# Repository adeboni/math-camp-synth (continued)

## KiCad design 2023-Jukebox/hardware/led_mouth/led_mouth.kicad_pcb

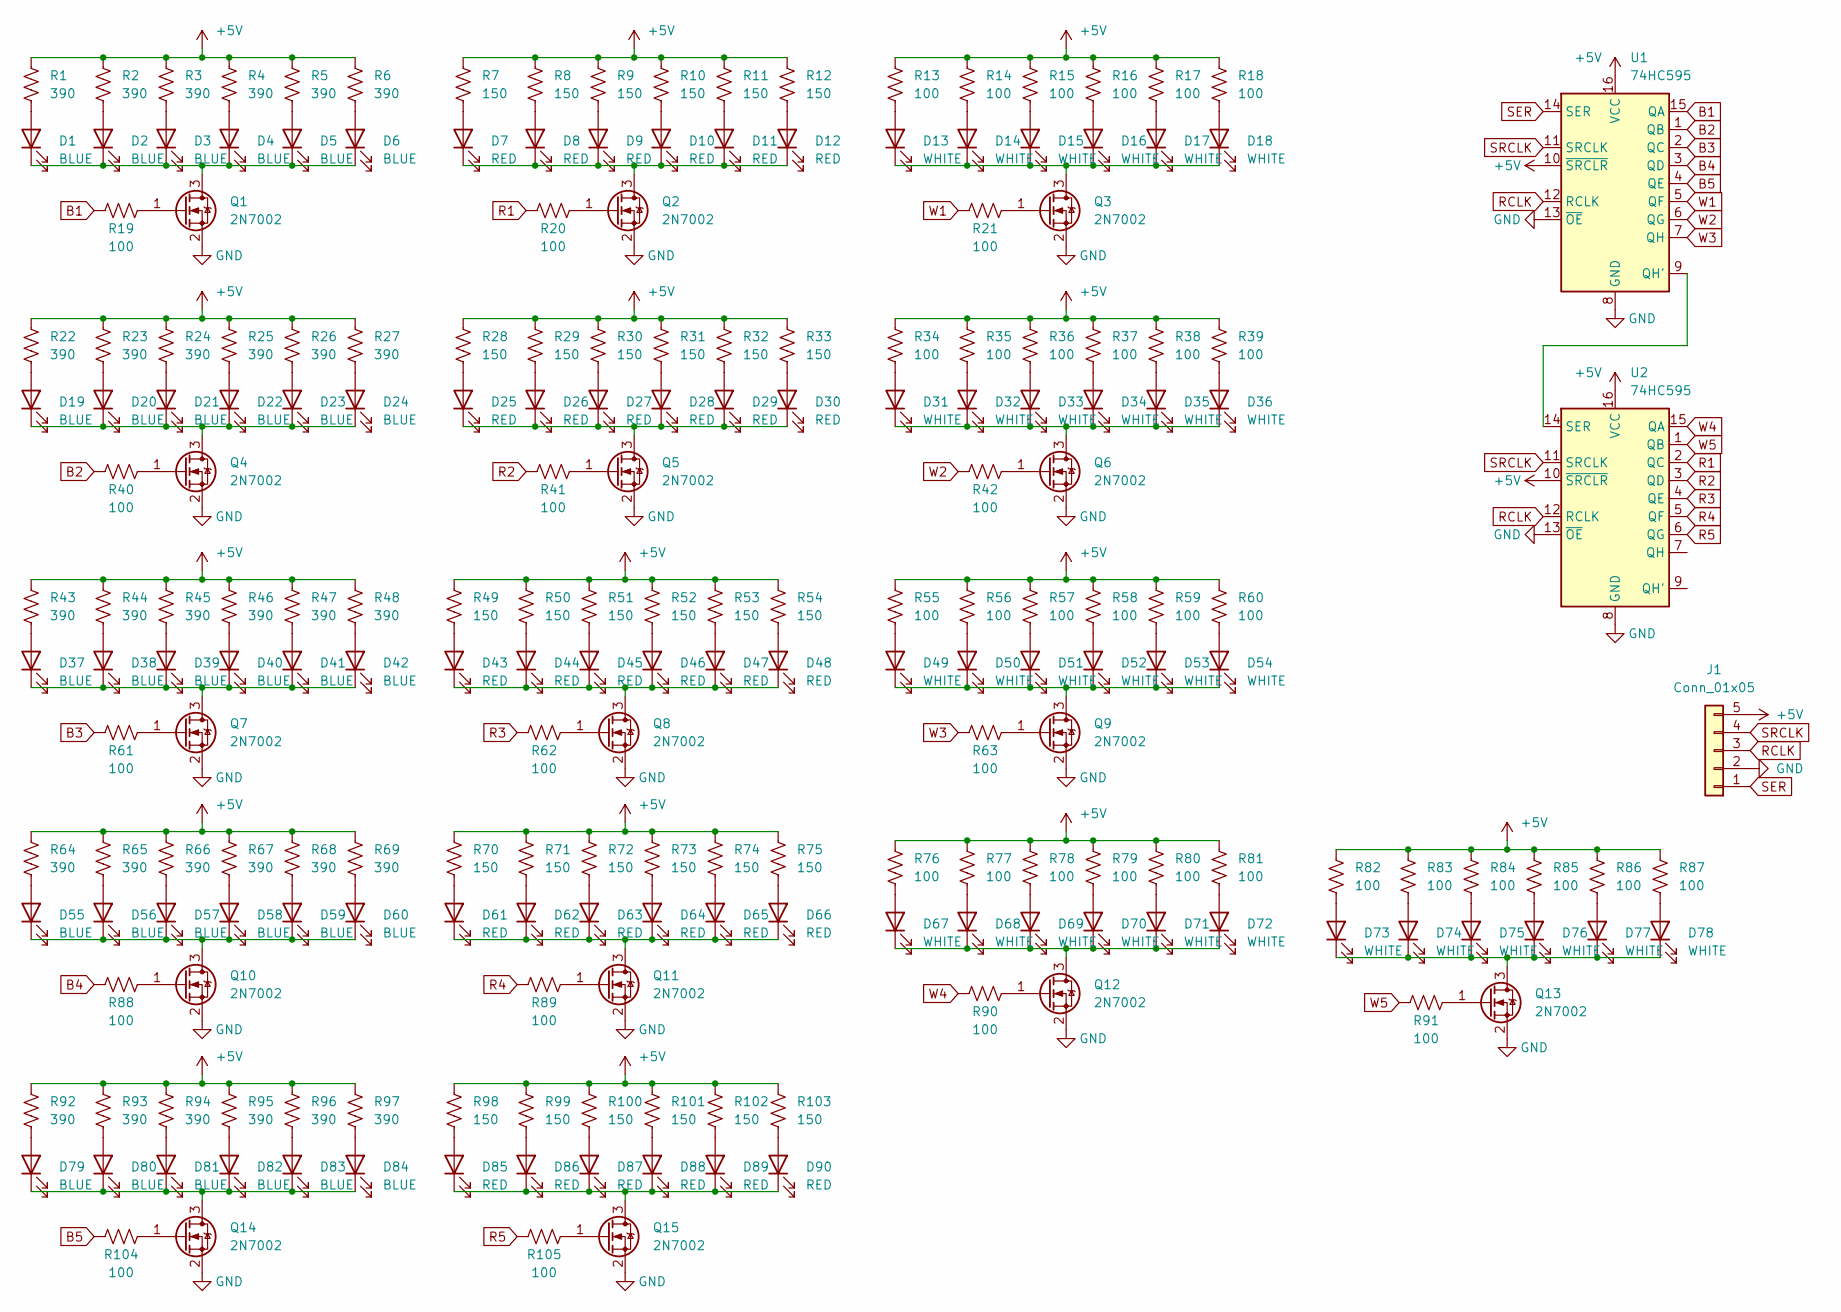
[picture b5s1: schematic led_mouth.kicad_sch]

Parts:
D1, D2, D3, D4, D5, D6, D19, D20, D21, D22, D23, D24, D37, D38, D39, D40, D41, D42, D55, D56, D57, D58, D59, D60, D79, D80, D81, D82, D83, D84: BLUE; LED_0603_1608Metric
D7, D8, D9, D10, D11, D12, D25, D26, D27, D28, D29, D30, D43, D44, D45, D46, D47, D48, D61, D62, D63, D64, D65, D66, D85, D86, D87, D88, D89, D90: RED; LED_0603_1608Metric
D13, D14, D15, D16, D17, D18, D31, D32, D33, D34, D35, D36, D49, D50, D51, D52, D53, D54, D67, D68, D69, D70, D71, D72, D73, D74, D75, D76, D77, D78: WHITE; LED_0603_1608Metric
J1: Conn_01x05
Q1, Q2, Q3, Q4, Q5, Q6, Q7, Q8, Q9, Q10, Q11, Q12, Q13, Q14, Q15: 2N7002; SOT-23
R1, R2, R3, R4, R5, R6, R22, R23, R24, R25, R26, R27, R43, R44, R45, R46, R47, R48, R64, R65, R66, R67, R68, R69, R92, R93, R94, R95, R96, R97: 390; R_0603_1608Metric
R7, R8, R9, R10, R11, R12, R28, R29, R30, R31, R32, R33, R49, R50, R51, R52, R53, R54, R70, R71, R72, R73, R74, R75, R98, R99, R100, R101, R102, R103: 150; R_0603_1608Metric
R13, R14, R15, R16, R17, R18, R20, R21, R34, R35, R36, R37, R38, R39, R40, R41, R42, R55, R56, R57, R58, R59, R60, R61, R62, R63, R76, R77, R78, R79, R80, R81, R82, R83, R84, R85, R86, R87, R88, R89, R90, R91, R104, R105: 100; R_0603_1608Metric
R19: 100
U1: 74HC595
U2: 74HC595; SOIC-16_3.9x9.9mm_P1.27mm

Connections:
+5V: J1.5, R1.2, R2.2, R3.2, R4.2, R5.2, R6.2, R7.2, R8.2, R9.2, R10.2, R11.2, R12.2, R13.2, R14.2, R15.2, R16.2, R17.2, R18.2, R22.2, R23.2, R24.2, R25.2, R26.2, R27.2, R28.2, R29.2, R30.2, R31.2, R32.2, R33.2, R34.2, R35.2, R36.2, R37.2, R38.2, R39.2, R43.2, R44.2, R45.2, R46.2, R47.2, R48.2, R49.2, R50.2, R51.2, R52.2, R53.2, R54.2, R55.2, R56.2, R57.2, R58.2, R59.2, R60.2, R64.2, R65.2, R66.2, R67.2, R68.2, R69.2, R70.2, R71.2, R72.2, R73.2, R74.2, R75.2, R76.2, R77.2, R78.2, R79.2, R80.2, R81.2, R82.2, R83.2, R84.2, R85.2, R86.2, R87.2, R92.2, R93.2, R94.2, R95.2, R96.2, R97.2, R98.2, R99.2, R100.2, R101.2, R102.2, R103.2, U1.10 (~SRCLR), U1.16 (VCC), U2.10 (~SRCLR), U2.16 (VCC)
B1: R19.1, U1.15 (QA)
B2: R40.1, U1.1 (QB)
B3: R61.1, U1.2 (QC)
B4: R88.1, U1.3 (QD)
B5: R104.1, U1.4 (QE)
GND: J1.2, Q1.2 (S), Q2.2 (S), Q3.2 (S), Q4.2 (S), Q5.2 (S), Q6.2 (S), Q7.2 (S), Q8.2 (S), Q9.2 (S), Q10.2 (S), Q11.2 (S), Q12.2 (S), Q13.2 (S), Q14.2 (S), Q15.2 (S), U1.8 (GND), U1.13 (~OE), U2.8 (GND), U2.13 (~OE)
unnamed: D1.1 (K), D2.1 (K), D3.1 (K), D4.1 (K), D5.1 (K), D6.1 (K), Q1.3 (D)
unnamed: D1.2 (A), R1.1
unnamed: D2.2 (A), R2.1
unnamed: D3.2 (A), R3.1
unnamed: D4.2 (A), R4.1
unnamed: D5.2 (A), R5.1
unnamed: D6.2 (A), R6.1
unnamed: D7.2 (A), R7.1
unnamed: D8.2 (A), R8.1
unnamed: D9.2 (A), R9.1
unnamed: D7.1 (K), D8.1 (K), D9.1 (K), D10.1 (K), D11.1 (K), D12.1 (K), Q2.3 (D)
unnamed: D10.2 (A), R10.1
unnamed: D11.2 (A), R11.1
unnamed: D12.2 (A), R12.1
unnamed: D13.1 (K), D14.1 (K), D15.1 (K), D16.1 (K), D17.1 (K), D18.1 (K), Q3.3 (D)
unnamed: D13.2 (A), R13.1
unnamed: D14.2 (A), R14.1
unnamed: D15.2 (A), R15.1
unnamed: D16.2 (A), R16.1
unnamed: D17.2 (A), R17.1
unnamed: D18.2 (A), R18.1
unnamed: D19.1 (K), D20.1 (K), D21.1 (K), D22.1 (K), D23.1 (K), D24.1 (K), Q4.3 (D)
unnamed: D19.2 (A), R22.1
unnamed: D20.2 (A), R23.1
unnamed: D21.2 (A), R24.1
unnamed: D22.2 (A), R25.1
unnamed: D23.2 (A), R26.1
unnamed: D24.2 (A), R27.1
unnamed: D25.1 (K), D26.1 (K), D27.1 (K), D28.1 (K), D29.1 (K), D30.1 (K), Q5.3 (D)
unnamed: D25.2 (A), R28.1
unnamed: D26.2 (A), R29.1
unnamed: D27.2 (A), R30.1
unnamed: D28.2 (A), R31.1
unnamed: D29.2 (A), R32.1
unnamed: D30.2 (A), R33.1
unnamed: D31.1 (K), D32.1 (K), D33.1 (K), D34.1 (K), D35.1 (K), D36.1 (K), Q6.3 (D)
unnamed: D31.2 (A), R34.1
unnamed: D32.2 (A), R35.1
unnamed: D33.2 (A), R36.1
unnamed: D34.2 (A), R37.1
unnamed: D35.2 (A), R38.1
unnamed: D36.2 (A), R39.1
unnamed: D37.1 (K), D38.1 (K), D39.1 (K), D40.1 (K), D41.1 (K), D42.1 (K), Q7.3 (D)
unnamed: D37.2 (A), R43.1
unnamed: D38.2 (A), R44.1
unnamed: D39.2 (A), R45.1
unnamed: D40.2 (A), R46.1
unnamed: D41.2 (A), R47.1
unnamed: D42.2 (A), R48.1
unnamed: D43.1 (K), D44.1 (K), D45.1 (K), D46.1 (K), D47.1 (K), D48.1 (K), Q8.3 (D)
unnamed: D43.2 (A), R49.1
unnamed: D44.2 (A), R50.1
unnamed: D45.2 (A), R51.1
unnamed: D46.2 (A), R52.1
unnamed: D47.2 (A), R53.1
unnamed: D48.2 (A), R54.1
unnamed: D49.1 (K), D50.1 (K), D51.1 (K), D52.1 (K), D53.1 (K), D54.1 (K), Q9.3 (D)
unnamed: D49.2 (A), R55.1
unnamed: D50.2 (A), R56.1
unnamed: D51.2 (A), R57.1
unnamed: D52.2 (A), R58.1
unnamed: D53.2 (A), R59.1
unnamed: D54.2 (A), R60.1
unnamed: D55.1 (K), D56.1 (K), D57.1 (K), D58.1 (K), D59.1 (K), D60.1 (K), Q10.3 (D)
unnamed: D55.2 (A), R64.1
unnamed: D56.2 (A), R65.1
unnamed: D57.2 (A), R66.1
unnamed: D58.2 (A), R67.1
unnamed: D59.2 (A), R68.1
unnamed: D60.2 (A), R69.1
unnamed: D61.1 (K), D62.1 (K), D63.1 (K), D64.1 (K), D65.1 (K), D66.1 (K), Q11.3 (D)
unnamed: D61.2 (A), R70.1
unnamed: D62.2 (A), R71.1
unnamed: D63.2 (A), R72.1
unnamed: D64.2 (A), R73.1
unnamed: D65.2 (A), R74.1
unnamed: D66.2 (A), R75.1
unnamed: D67.1 (K), D68.1 (K), D69.1 (K), D70.1 (K), D71.1 (K), D72.1 (K), Q12.3 (D)
unnamed: D67.2 (A), R76.1
unnamed: D68.2 (A), R77.1
unnamed: D69.2 (A), R78.1
unnamed: D70.2 (A), R79.1
unnamed: D71.2 (A), R80.1
unnamed: D72.2 (A), R81.1
unnamed: D73.1 (K), D74.1 (K), D75.1 (K), D76.1 (K), D77.1 (K), D78.1 (K), Q13.3 (D)
unnamed: D73.2 (A), R82.1
unnamed: D74.2 (A), R83.1
unnamed: D75.2 (A), R84.1
unnamed: D76.2 (A), R85.1
unnamed: D77.2 (A), R86.1
unnamed: D78.2 (A), R87.1
unnamed: D79.1 (K), D80.1 (K), D81.1 (K), D82.1 (K), D83.1 (K), D84.1 (K), Q14.3 (D)
unnamed: D79.2 (A), R92.1
unnamed: D80.2 (A), R93.1
unnamed: D81.2 (A), R94.1
unnamed: D82.2 (A), R95.1
unnamed: D83.2 (A), R96.1
unnamed: D84.2 (A), R97.1
unnamed: D85.1 (K), D86.1 (K), D87.1 (K), D88.1 (K), D89.1 (K), D90.1 (K), Q15.3 (D)
unnamed: D85.2 (A), R98.1
unnamed: D86.2 (A), R99.1
unnamed: D87.2 (A), R100.1
unnamed: D88.2 (A), R101.1
unnamed: D89.2 (A), R102.1
unnamed: D90.2 (A), R103.1
unnamed: Q1.1 (G), R19.2
unnamed: Q2.1 (G), R20.2
unnamed: Q3.1 (G), R21.2
unnamed: Q4.1 (G), R40.2
unnamed: Q5.1 (G), R41.2
unnamed: Q6.1 (G), R42.2
unnamed: Q7.1 (G), R61.2
unnamed: Q8.1 (G), R62.2
unnamed: Q9.1 (G), R63.2
unnamed: Q10.1 (G), R88.2
unnamed: Q11.1 (G), R89.2
unnamed: Q12.1 (G), R90.2
unnamed: Q13.1 (G), R91.2
unnamed: Q14.1 (G), R104.2
unnamed: Q15.1 (G), R105.2
unnamed: U1.9 (QH'), U2.14 (SER)
R1: R20.1, U2.2 (QC)
R2: R41.1, U2.3 (QD)
R3: R62.1, U2.4 (QE)
R4: R89.1, U2.5 (QF)
R5: R105.1, U2.6 (QG)
RCLK: J1.3, U1.12 (RCLK), U2.12 (RCLK)
SER: J1.1, U1.14 (SER)
SRCLK: J1.4, U1.11 (SRCLK), U2.11 (SRCLK)
W1: R21.1, U1.5 (QF)
W2: R42.1, U1.6 (QG)
W3: R63.1, U1.7 (QH)
W4: R90.1, U2.15 (QA)
W5: R91.1, U2.1 (QB)

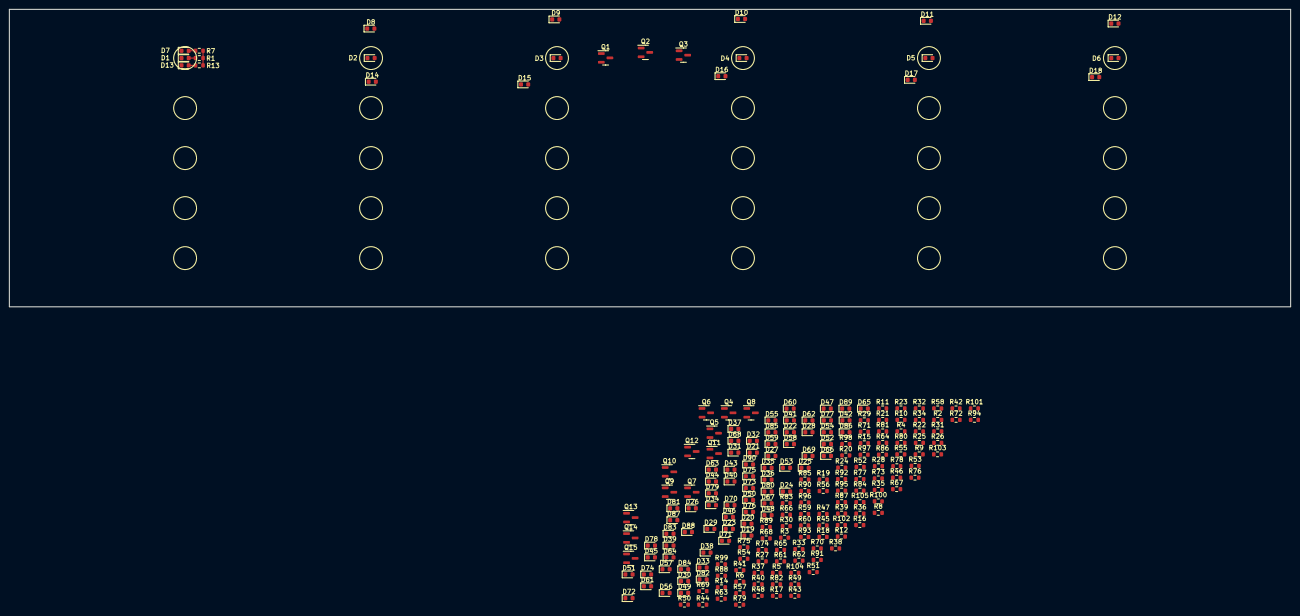
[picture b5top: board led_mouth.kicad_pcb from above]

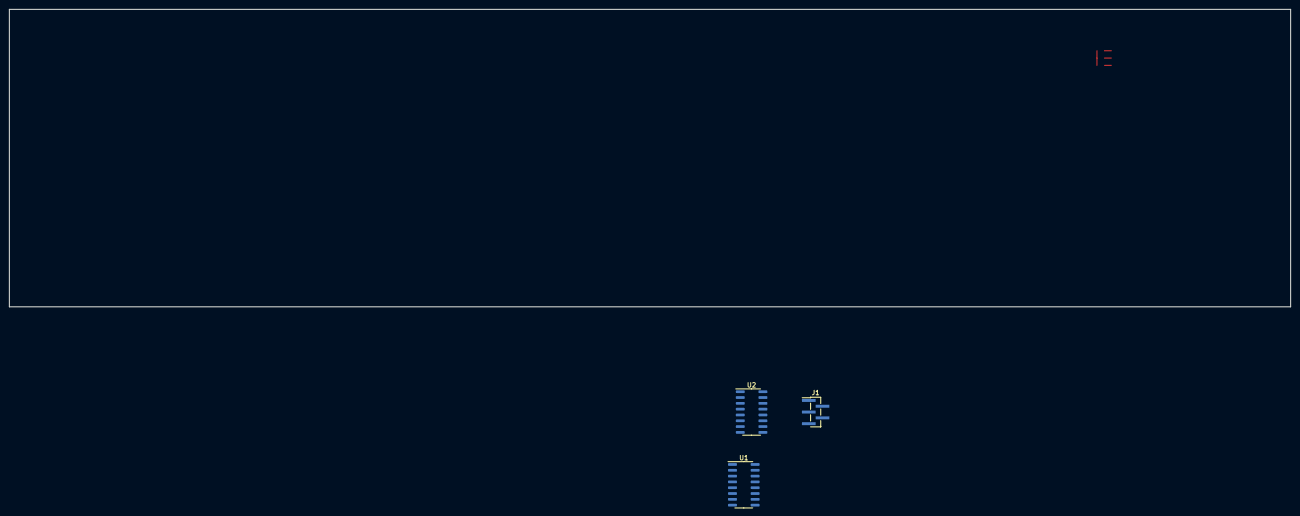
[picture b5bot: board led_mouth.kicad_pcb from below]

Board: 2 copper layers, 280.0 x 65.0 mm, 213 parts (3 on the bottom side), 141 nets.

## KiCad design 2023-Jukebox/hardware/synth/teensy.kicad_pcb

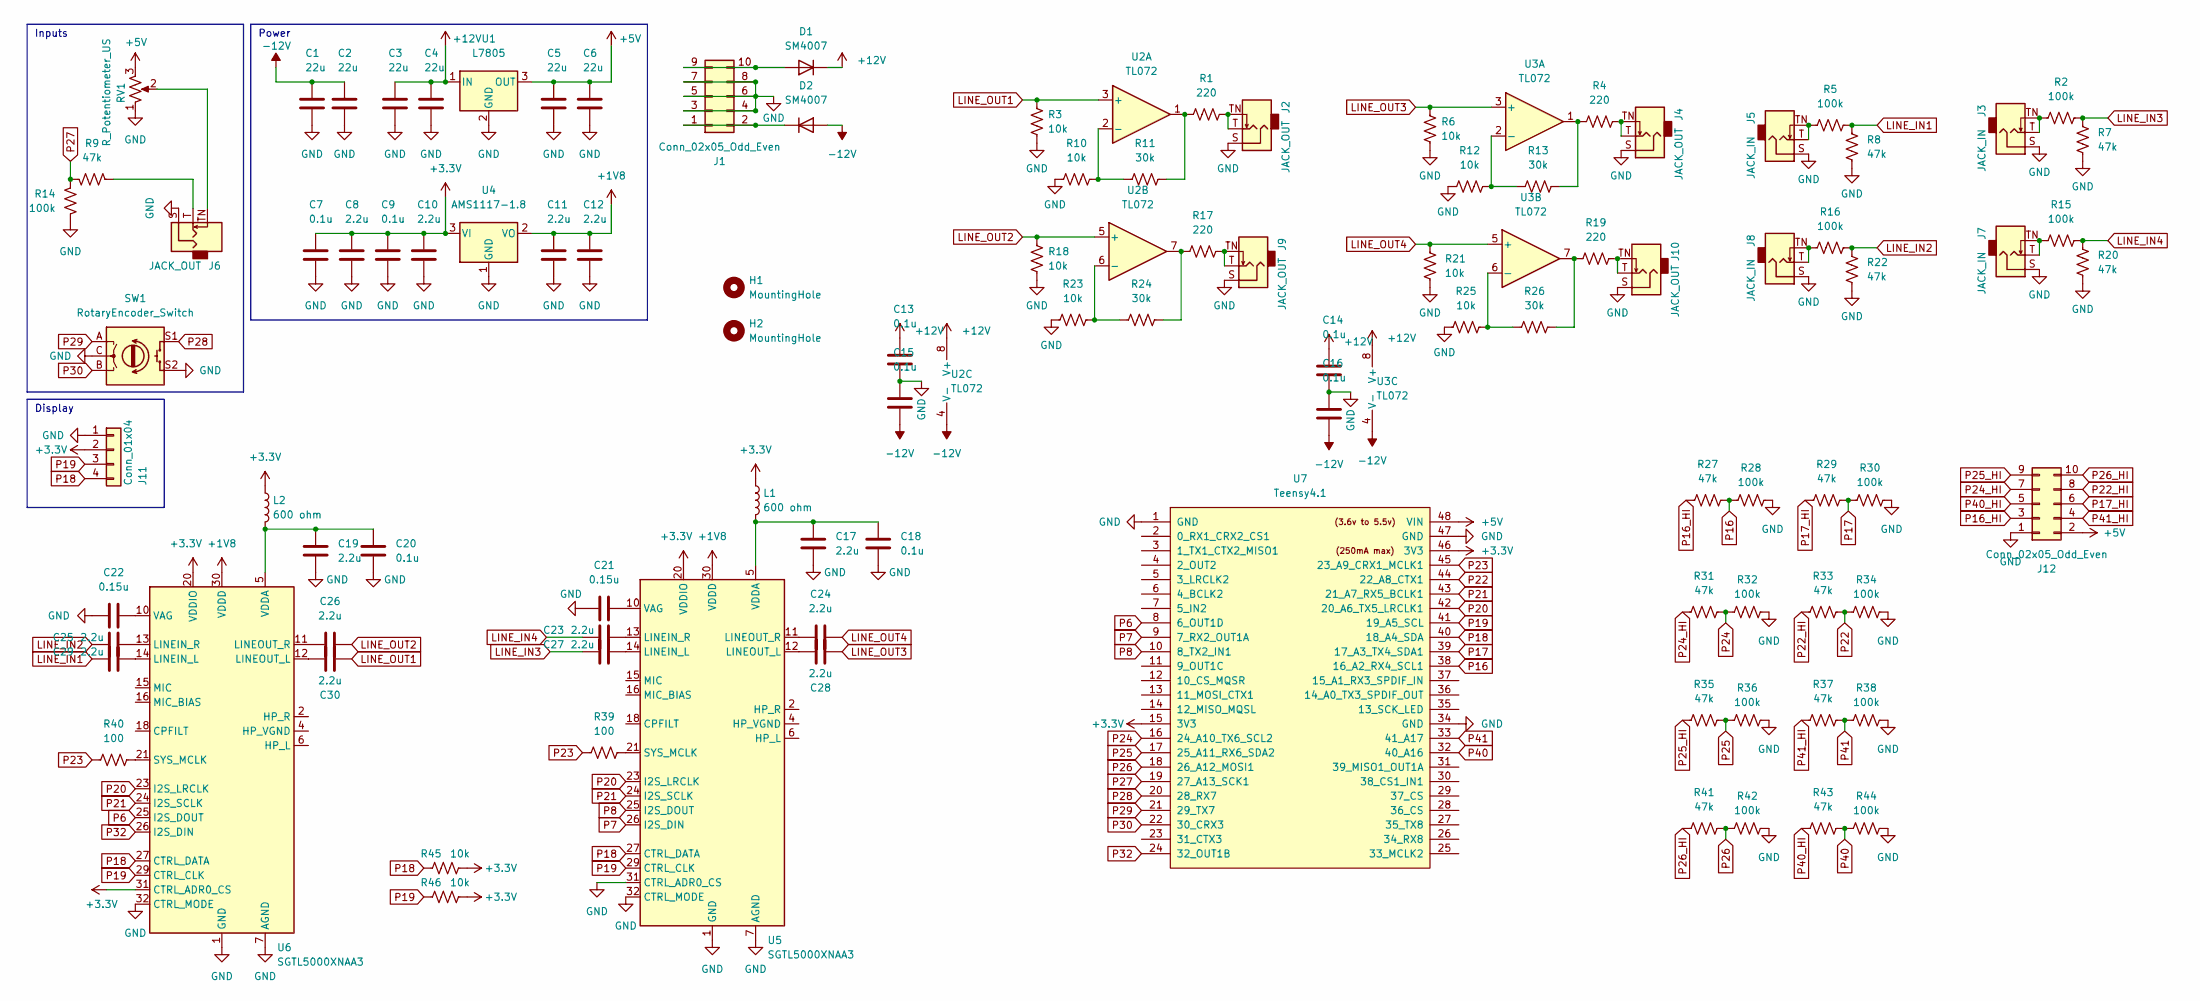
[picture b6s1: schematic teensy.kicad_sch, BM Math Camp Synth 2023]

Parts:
C1, C2, C3, C4, C5, C6: 22u; C_0805_2012Metric
C7, C9, C13, C14, C15, C16, C18, C20: 0.1u; C_0603_1608Metric
C8, C10, C11, C12, C17, C19, C23, C24, C25, C26, C27, C28, C29, C30: 2.2u; C_0603_1608Metric
C21, C22: 0.15u; C_0603_1608Metric
D1, D2: SM4007; D_SOD-123
H1, H2: MountingHole; MountingHole_2.2mm_M2
J1, J12: Conn_02x05_Odd_Even; IDC-Header_2x05_P2.54mm_Vertical
J2, J4, J6, J9, J10: JACK_OUT; Jack_3.5mm_QingPu_WQP-PJ398SM_Vertical_CircularHoles
J3, J5, J7, J8: JACK_IN; Jack_3.5mm_QingPu_WQP-PJ398SM_Vertical_CircularHoles
J11: Conn_01x04; SSD1106
L1, L2: 600 ohm; L_0603_1608Metric
R1, R4, R17, R19: 220; R_0603_1608Metric
R2, R5, R14, R15, R16, R28, R30, R32, R34, R36, R38, R42, R44: 100k; R_0603_1608Metric
R3, R6, R10, R12, R18, R21, R23, R25, R45, R46: 10k; R_0603_1608Metric
R7, R8, R9, R20, R22, R27, R29, R31, R33, R35, R37, R41, R43: 47k; R_0603_1608Metric
R11, R13, R24, R26: 30k; R_0603_1608Metric
R39, R40: 100; R_0603_1608Metric
RV1: R_Potentiometer_US; Potentiometer_Alpha_RD901F-40-00D_Single_Vertical
SW1: RotaryEncoder_Switch; RotaryEncoder_Alps_EC11E-Switch_Vertical_H20mm
U1: L7805; TO-252-2
U2, U3: TL072; SOIC-8_3.9x4.9mm_P1.27mm
U4: AMS1117-1.8; SOT-223-3_TabPin2
U5, U6: SGTL5000XNAA3; QFN-32-1EP_5x5mm_P0.5mm_EP3.6x3.6mm
U7: Teensy4.1; Teensy41

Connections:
+1V8: C11.1, C12.1, U4.2 (VO), U5.30 (VDDD), U6.30 (VDDD)
+3V3: C7.1, C8.1, C9.1, C10.1, J11.2, L1.1, L2.1, R45.2, R46.2, U4.3 (VI), U5.20 (VDDIO), U6.20 (VDDIO), U6.31 (CTRL_ADR0_CS), U7.15 (3V3), U7.46 (3V3)
+5V: C5.1, C6.1, J12.2, RV1.3, U1.3 (OUT), U7.48 (VIN)
+12V: C3.1, C4.1, C13.1, C14.1, D1.1 (K), U1.1 (IN), U2.8 (V+), U3.8 (V+)
-12V: C1.1, C2.1, C15.2, C16.2, D2.2 (A), U2.4 (V-), U3.4 (V-)
GND: C1.2, C2.2, C3.2, C4.2, C5.2, C6.2, C7.2, C8.2, C9.2, C10.2, C11.2, C12.2, C13.2, C14.2, C15.1, C16.1, C17.2, C18.2, C19.2, C20.2, C21.1, C22.1, J1.3, J1.4, J1.5, J1.6, J1.7, J1.8, J2.S, J3.S, J4.S, J5.S, J6.S, J7.S, J8.S, J9.S, J10.S, J11.1, J12.1, R3.1, R6.1, R7.1, R8.1, R10.1, R12.1, R14.1, R18.1, R20.1, R21.1, R22.1, R23.1, R25.1, R28.1, R30.1, R32.1, R34.1, R36.1, R38.1, R42.1, R44.1, RV1.1, SW1.C, SW1.S2, U1.2 (GND), U4.1 (GND), U5.1 (GND), U5.3 (GND), U5.7 (AGND), U5.31 (CTRL_ADR0_CS), U5.32 (CTRL_MODE), U5.33 (GND), U6.1 (GND), U6.3 (GND), U6.7 (AGND), U6.32 (CTRL_MODE), U6.33 (GND), U7.1 (GND), U7.34 (GND), U7.47 (GND)
LINE_IN1: C29.1, R5.2, R8.2
LINE_IN2: C25.1, R16.2, R22.2
LINE_IN3: C27.1, R2.2, R7.2
LINE_IN4: C23.1, R15.2, R20.2
LINE_OUT1: C30.2, R3.2, U2.3 (+)
LINE_OUT2: C26.2, R18.2, U2.5 (+)
LINE_OUT3: C28.2, R6.2, U3.3 (+)
LINE_OUT4: C24.2, R21.2, U3.5 (+)
unnamed: C17.1, C18.1, L1.2, U5.5 (VDDA)
unnamed: C19.1, C20.1, L2.2, U6.5 (VDDA)
unnamed: C21.2, U5.10 (VAG)
unnamed: C22.2, U6.10 (VAG)
unnamed: C23.2, U5.13 (LINEIN_R)
unnamed: C24.1, U5.11 (LINEOUT_R)
unnamed: C25.2, U6.13 (LINEIN_R)
unnamed: C26.1, U6.11 (LINEOUT_R)
unnamed: C27.2, U5.14 (LINEIN_L)
unnamed: C28.1, U5.12 (LINEOUT_L)
unnamed: C29.2, U6.14 (LINEIN_L)
unnamed: C30.1, U6.12 (LINEOUT_L)
unnamed: D1.2 (A), J1.9, J1.10
unnamed: D2.1 (K), J1.1, J1.2
unnamed: J2.T, J2.TN, R1.2
unnamed: J3.T, J3.TN, R2.1
unnamed: J4.T, J4.TN, R4.2
unnamed: J5.T, J5.TN, R5.1
unnamed: J6.T, R9.1
unnamed: J6.TN, RV1.2
unnamed: J7.T, J7.TN, R15.1
unnamed: J8.T, J8.TN, R16.1
unnamed: J9.T, J9.TN, R17.2
unnamed: J10.T, J10.TN, R19.2
unnamed: R1.1, R11.2, U2.1
unnamed: R10.2, R11.1, U2.2 (-)
unnamed: R12.2, R13.1, U3.2 (-)
unnamed: R4.1, R13.2, U3.1
unnamed: R17.1, R24.2, U2.7
unnamed: R19.1, R26.2, U3.7
unnamed: R23.2, R24.1, U2.6 (-)
unnamed: R25.2, R26.1, U3.6 (-)
unnamed: R39.2, U5.21 (SYS_MCLK)
unnamed: R40.2, U6.21 (SYS_MCLK)
P6: U6.25 (I2S_DOUT), U7.8 (6_OUT1D)
P7: U5.26 (I2S_DIN), U7.9 (7_RX2_OUT1A)
P8: U5.25 (I2S_DOUT), U7.10 (8_TX2_IN1)
P16: R27.2, R28.2, U7.38 (16_A2_RX4_SCL1)
P16_HI: J12.3, R27.1
P17: R29.2, R30.2, U7.39 (17_A3_TX4_SDA1)
P17_HI: J12.6, R29.1
P18: J11.4, R45.1, U5.27 (CTRL_DATA), U6.27 (CTRL_DATA), U7.40 (18_A4_SDA)
P19: J11.3, R46.1, U5.29 (CTRL_CLK), U6.29 (CTRL_CLK), U7.41 (19_A5_SCL)
P20: U5.23 (I2S_LRCLK), U6.23 (I2S_LRCLK), U7.42 (20_A6_TX5_LRCLK1)
P21: U5.24 (I2S_SCLK), U6.24 (I2S_SCLK), U7.43 (21_A7_RX5_BCLK1)
P22: R33.2, R34.2, U7.44 (22_A8_CTX1)
P22_HI: J12.8, R33.1
P23: R39.1, R40.1, U7.45 (23_A9_CRX1_MCLK1)
P24: R31.2, R32.2, U7.16 (24_A10_TX6_SCL2)
P24_HI: J12.7, R31.1
P25: R35.2, R36.2, U7.17 (25_A11_RX6_SDA2)
P25_HI: J12.9, R35.1
P26: R41.2, R42.2, U7.18 (26_A12_MOSI1)
P26_HI: J12.10, R41.1
P27: R9.2, R14.2, U7.19 (27_A13_SCK1)
P28: SW1.S1, U7.20 (28_RX7)
P29: SW1.A, U7.21 (29_TX7)
P30: SW1.B, U7.22 (30_CRX3)
P32: U6.26 (I2S_DIN), U7.24 (32_OUT1B)
P40: R43.2, R44.2, U7.32 (40_A16)
P40_HI: J12.5, R43.1
P41: R37.2, R38.2, U7.33 (41_A17)
P41_HI: J12.4, R37.1

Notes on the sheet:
Display
Inputs
Power

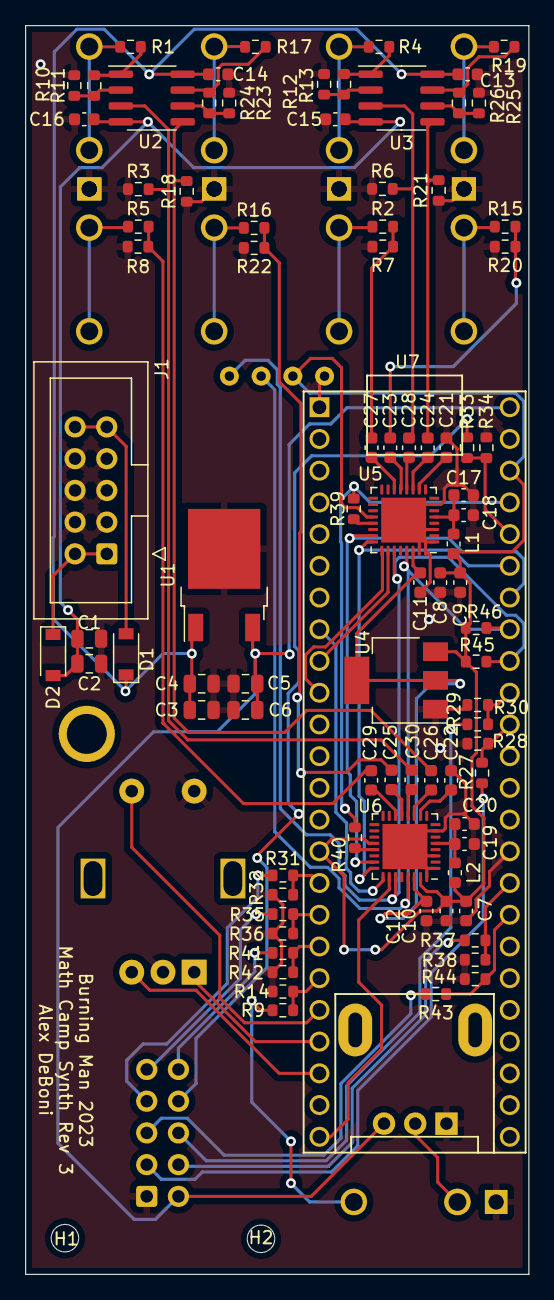
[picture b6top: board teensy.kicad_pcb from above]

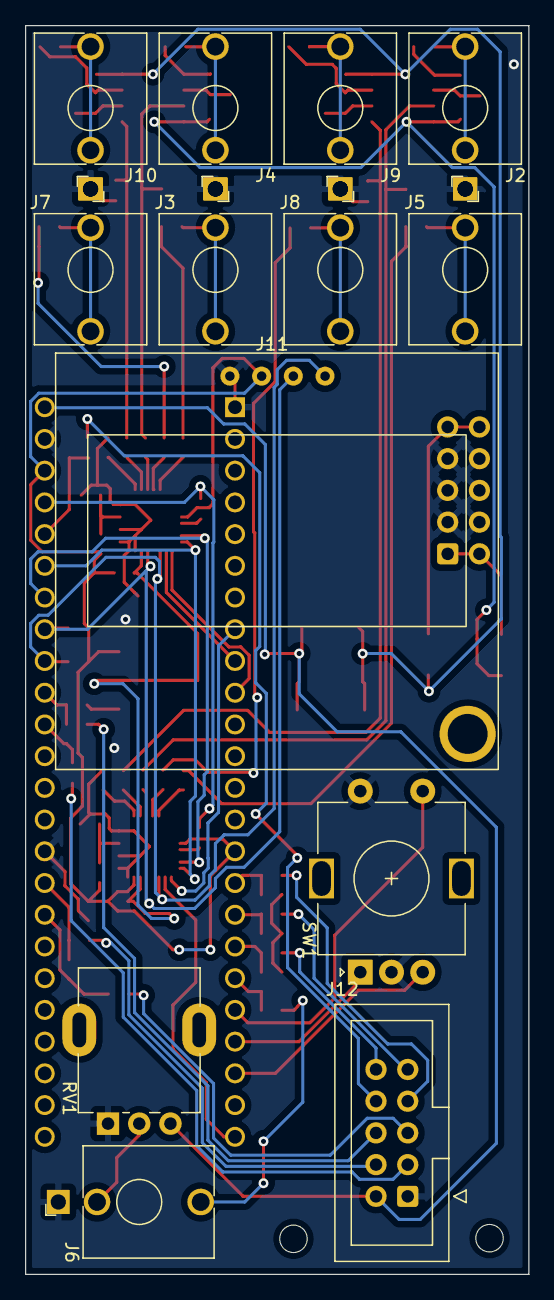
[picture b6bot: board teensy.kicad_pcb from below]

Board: 2 copper layers, 40.3 x 100.0 mm, 103 parts (13 on the bottom side), 77 nets.
